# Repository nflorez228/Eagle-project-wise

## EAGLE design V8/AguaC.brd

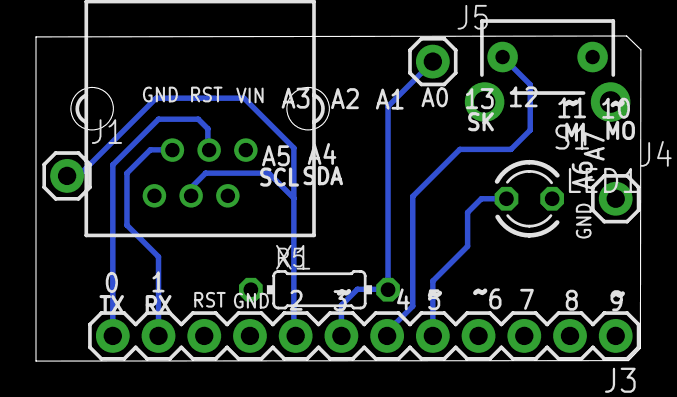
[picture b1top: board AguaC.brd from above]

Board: 2 copper layers, 33.6 x 18.1 mm, 8 parts (0 on the bottom side), 8 nets.

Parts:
J1, J4, J5: 1X01
J3: 1X12
LED1: LED3MM
R5: 0204/7
S1: SWITCH-MOMENTARY-2SIDE_EZ; TACTILE-PTH-SIDEEZ
X1: YH-55-10

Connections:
AGND: J4.1, LED1.K, S1.1
GND: J3.9, R5.1, X1.2
unnamed: J3.6, S1.2
unnamed: J3.5, LED1.A
unnamed: J3.12, X1.3
unnamed: J3.11, X1.5
unnamed: J3.7, J5.1, R5.2
VIN: J1.1, J3.8, X1.4

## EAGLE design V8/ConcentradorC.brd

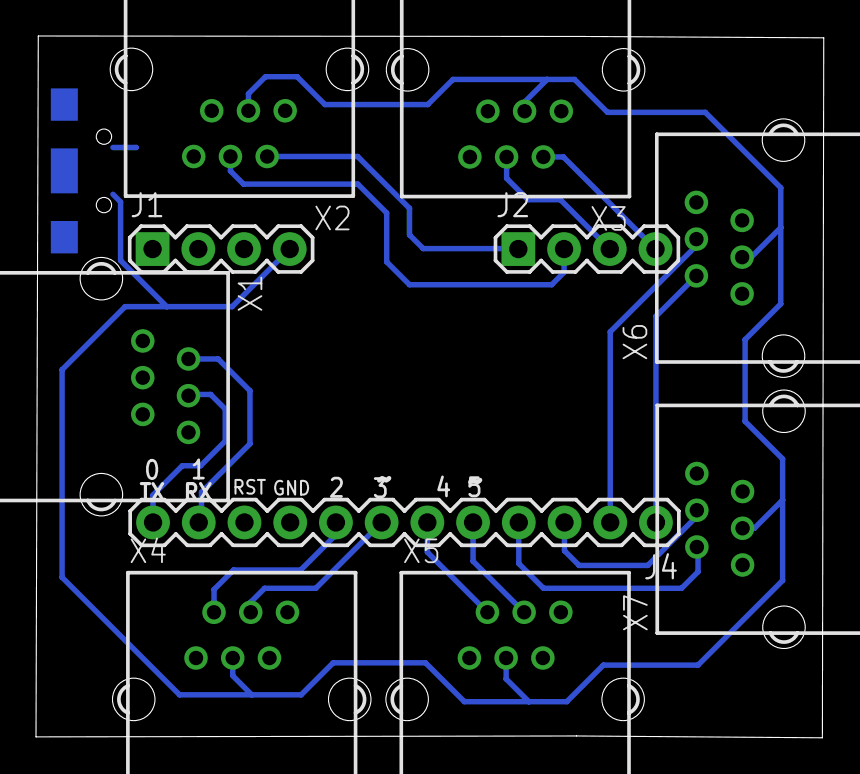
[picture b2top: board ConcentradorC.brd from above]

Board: 2 copper layers, 43.8 x 39.0 mm, 11 parts (1 on the bottom side), 16 nets.

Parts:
J1, J2: 1X04
J4: 1X12
JP9: Micro USB; USB-AB-MICRO-SMD_V03
X1, X2, X3, X4, X5, X6, X7: YH-55-10

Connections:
GND: J1.2, J4.9, JP9.GND1, X1.5, X2.5, X3.5, X4.5, X5.5, X6.5, X7.5
unnamed: J4.5, X5.4
unnamed: J4.6, X5.2
unnamed: J4.3, X7.4
unnamed: J4.12, X1.4
unnamed: J4.11, X1.2
unnamed: J4.4, X7.2
unnamed: J4.7, X4.4
unnamed: J4.8, X4.2
unnamed: J4.2, X6.4
unnamed: J4.1, X6.2
unnamed: J2.4, X3.2
unnamed: J2.3, X3.4
unnamed: J2.2, X2.4
unnamed: J2.1, X2.2
VIN: J1.4, JP9.VBUS1, X2.3, X3.3, X4.3, X5.3, X6.3, X7.3

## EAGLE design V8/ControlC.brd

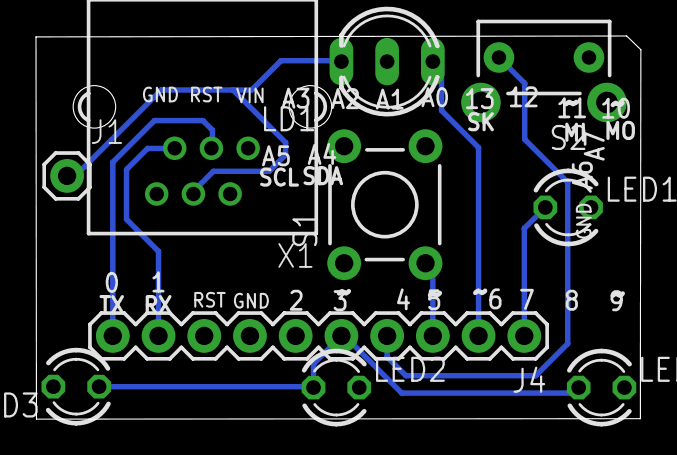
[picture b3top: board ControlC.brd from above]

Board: 2 copper layers, 33.6 x 21.3 mm, 10 parts (0 on the bottom side), 9 nets.

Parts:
J1: 1X01
J4: 1X10
LD1: DUOLED-A-5MM
LED1, LED2, LED3, LED4: LED3MM
S1: TACTILE-PTH
S2: SWITCH-MOMENTARY-2SIDE_EZ; TACTILE-PTH-SIDEEZ
X1: YH-55-10

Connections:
AGND: J4.7, LD1.A, LED1.K, LED2.K, LED3.K, LED4.K, S1.1, S1.2, S2.1
unnamed: J4.4, S2.2
unnamed: J4.2, LD1.CX
unnamed: J4.3, S1.3
unnamed: J1.1, LD1.CR, X1.4
unnamed: J4.5, LED2.A, LED3.A, LED4.A
unnamed: J4.9, X1.5
unnamed: J4.1, LED1.A
VIN: J4.10, X1.3

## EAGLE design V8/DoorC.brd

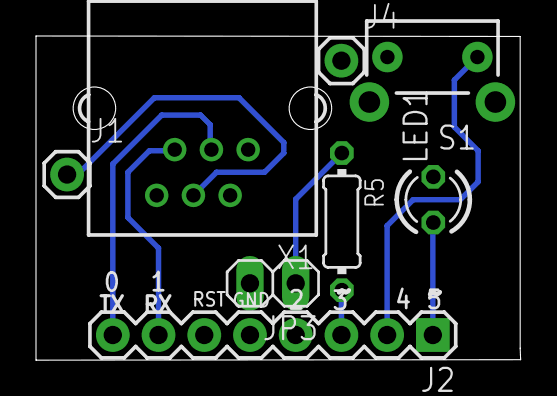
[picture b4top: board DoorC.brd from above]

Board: 2 copper layers, 26.9 x 18.0 mm, 8 parts (0 on the bottom side), 8 nets.

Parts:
J1, J4: 1X01
J2: 1X08
JP3: 1X02
LED1: LED3MM
R5: 0204/7
S1: SWITCH-MOMENTARY-2SIDE_EZ; TACTILE-PTH-SIDEEZ
X1: YH-55-10

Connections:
GND: J2.5, JP3.2, LED1.K, S1.2, X1.2
unnamed: J2.2, S1.1
unnamed: JP3.1, R5.1
unnamed: J2.1, LED1.A
unnamed: J2.8, X1.3
unnamed: J2.7, X1.5
unnamed: J2.3, R5.2
VIN: J1.1, X1.4

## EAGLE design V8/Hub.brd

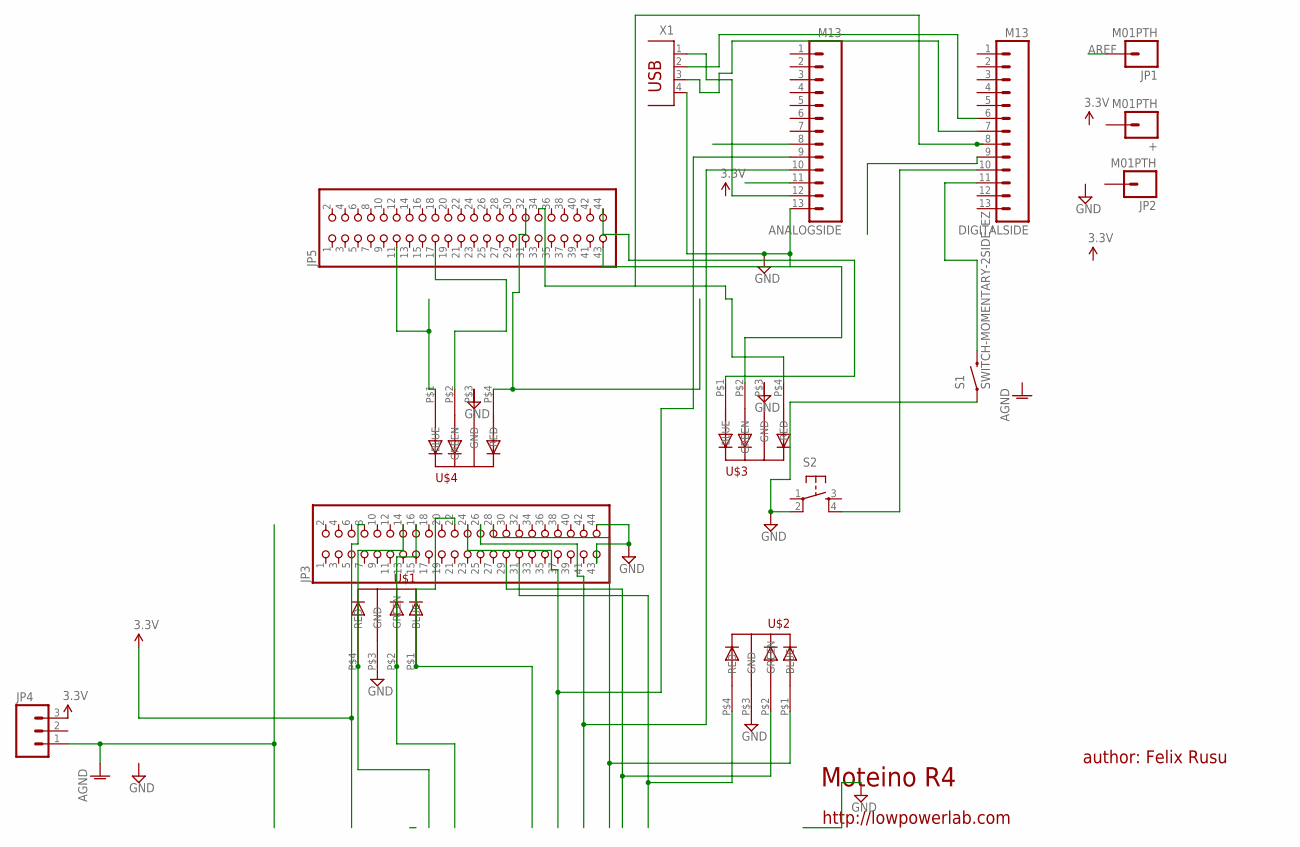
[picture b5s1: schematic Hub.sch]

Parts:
+: M01PTH; 1X01
ANALOGSIDE: M13; 1X13
DIGITALSIDE: M13; 1X13
JP1, JP2: M01PTH; 1X01
JP3, JP5: PINHD-2X22; 2X22
JP4: M03PTH; 1X03
S1: SWITCH-MOMENTARY-2SIDE_EZ; TACTILE-PTH-SIDEEZ
S2: TAC_SWITCHPTH; TACTILE-PTH
U$1, U$2, U$3, U$4: 5MMRGBLED; LED5MMRGB
X1: PN87520

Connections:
AGND: JP4.1
AREF: JP1.1
GND: ANALOGSIDE.13, JP3.43, JP3.44, S1.1, S2.2, U$1.P$3 (GND), U$2.P$3 (GND), U$3.P$3 (GND), U$4.P$3 (GND), X1.4
unnamed: DIGITALSIDE.10, S2.4
unnamed: ANALOGSIDE.9, JP3.24
unnamed: JP3.14, U$1.P$4 (RED)
unnamed: JP3.16, U$1.P$2 (GREEN)
unnamed: DIGITALSIDE.11, S1.2
unnamed: JP3.22, U$1.P$1 (BLUE)
unnamed: JP3.28, U$2.P$1 (BLUE)
unnamed: JP3.29, U$2.P$2 (GREEN)
unnamed: JP3.31, U$2.P$4 (RED)
unnamed: JP5.11, U$4.P$1 (BLUE)
unnamed: JP5.17, U$4.P$2 (GREEN)
unnamed: JP5.32, U$4.P$4 (RED)
unnamed: JP5.43, U$3.P$2 (GREEN)
unnamed: JP5.44, U$3.P$1 (BLUE)
unnamed: JP5.34, U$3.P$4 (RED)
unnamed: ANALOGSIDE.10, JP3.26
unnamed: DIGITALSIDE.7, X1.3
unnamed: ANALOGSIDE.12, X1.1
unnamed: DIGITALSIDE.6, X1.2
VCC: JP3.8, JP4.3

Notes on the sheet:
Moteino R4
author: Felix Rusu
http://lowpowerlab.com

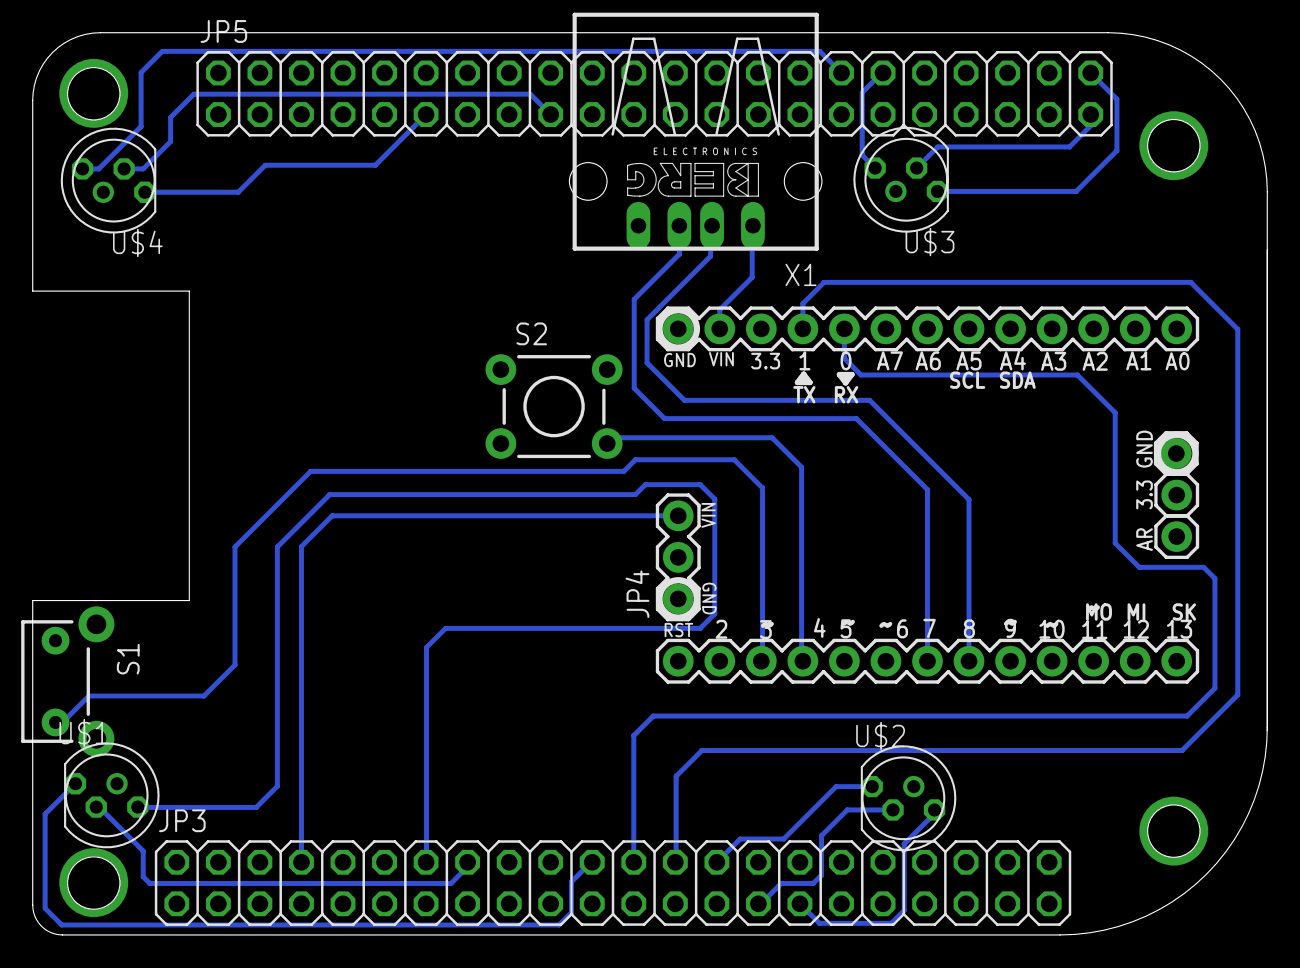
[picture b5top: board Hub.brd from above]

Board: 2 copper layers, 75.5 x 55.2 mm, 15 parts (0 on the bottom side), 21 nets.

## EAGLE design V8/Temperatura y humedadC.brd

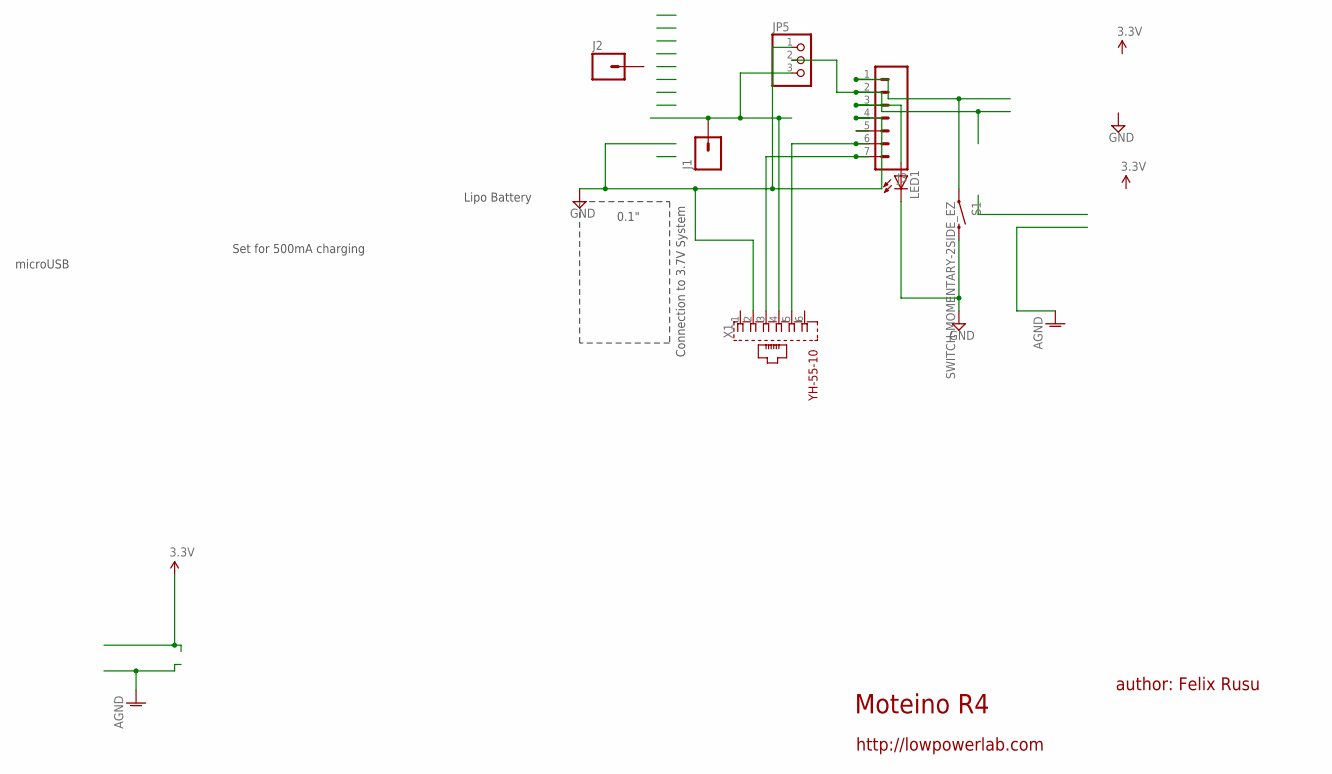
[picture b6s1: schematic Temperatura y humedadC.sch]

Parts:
J1, J2: M01PTH; 1X01
J3: M07; 1X07
JP5: PINHD-1X3; 1X03
LED1: LED3MM
S1: SWITCH-MOMENTARY-2SIDE_EZ; TACTILE-PTH-SIDEEZ
X1: YH-55-10

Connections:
GND: J3.4, JP5.1, LED1.K (C), S1.2, X1.2
unnamed: J3.1, S1.1
unnamed: J3.3, LED1.A
unnamed: J3.7, X1.3
unnamed: J3.6, X1.5
unnamed: J3.2, JP5.2
VIN: J1.1, JP5.3, X1.4

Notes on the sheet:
Moteino R4
author: Felix Rusu
http://lowpowerlab.com
Set for 500mA charging
Connection to 3.7V System
0.1"
microUSB
Lipo Battery

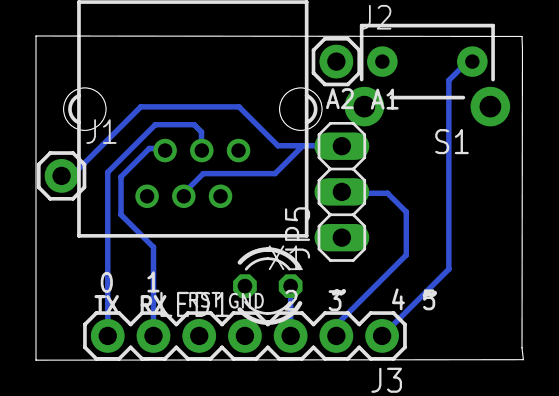
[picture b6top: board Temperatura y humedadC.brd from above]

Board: 2 copper layers, 27.1 x 18.0 mm, 7 parts (0 on the bottom side), 7 nets.

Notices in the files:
parts and their libraries:
SparkFun-Connectors: Licensing: CC v3.0 Share-Alike You are welcome to use this library for commercial purposes.
SparkFun-Electromechanical: Licensing: Creative Commons ShareAlike 4.0 International - https://creativecommons.org/licenses/by-sa/4.0
